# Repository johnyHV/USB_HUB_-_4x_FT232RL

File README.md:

# USB_HUB_-_4x_FT232RL

- USB HUB with FE1.1 chip
- 4x FTDI FT-232RL chip
- 1,8V, 3,3V, 5V logic level

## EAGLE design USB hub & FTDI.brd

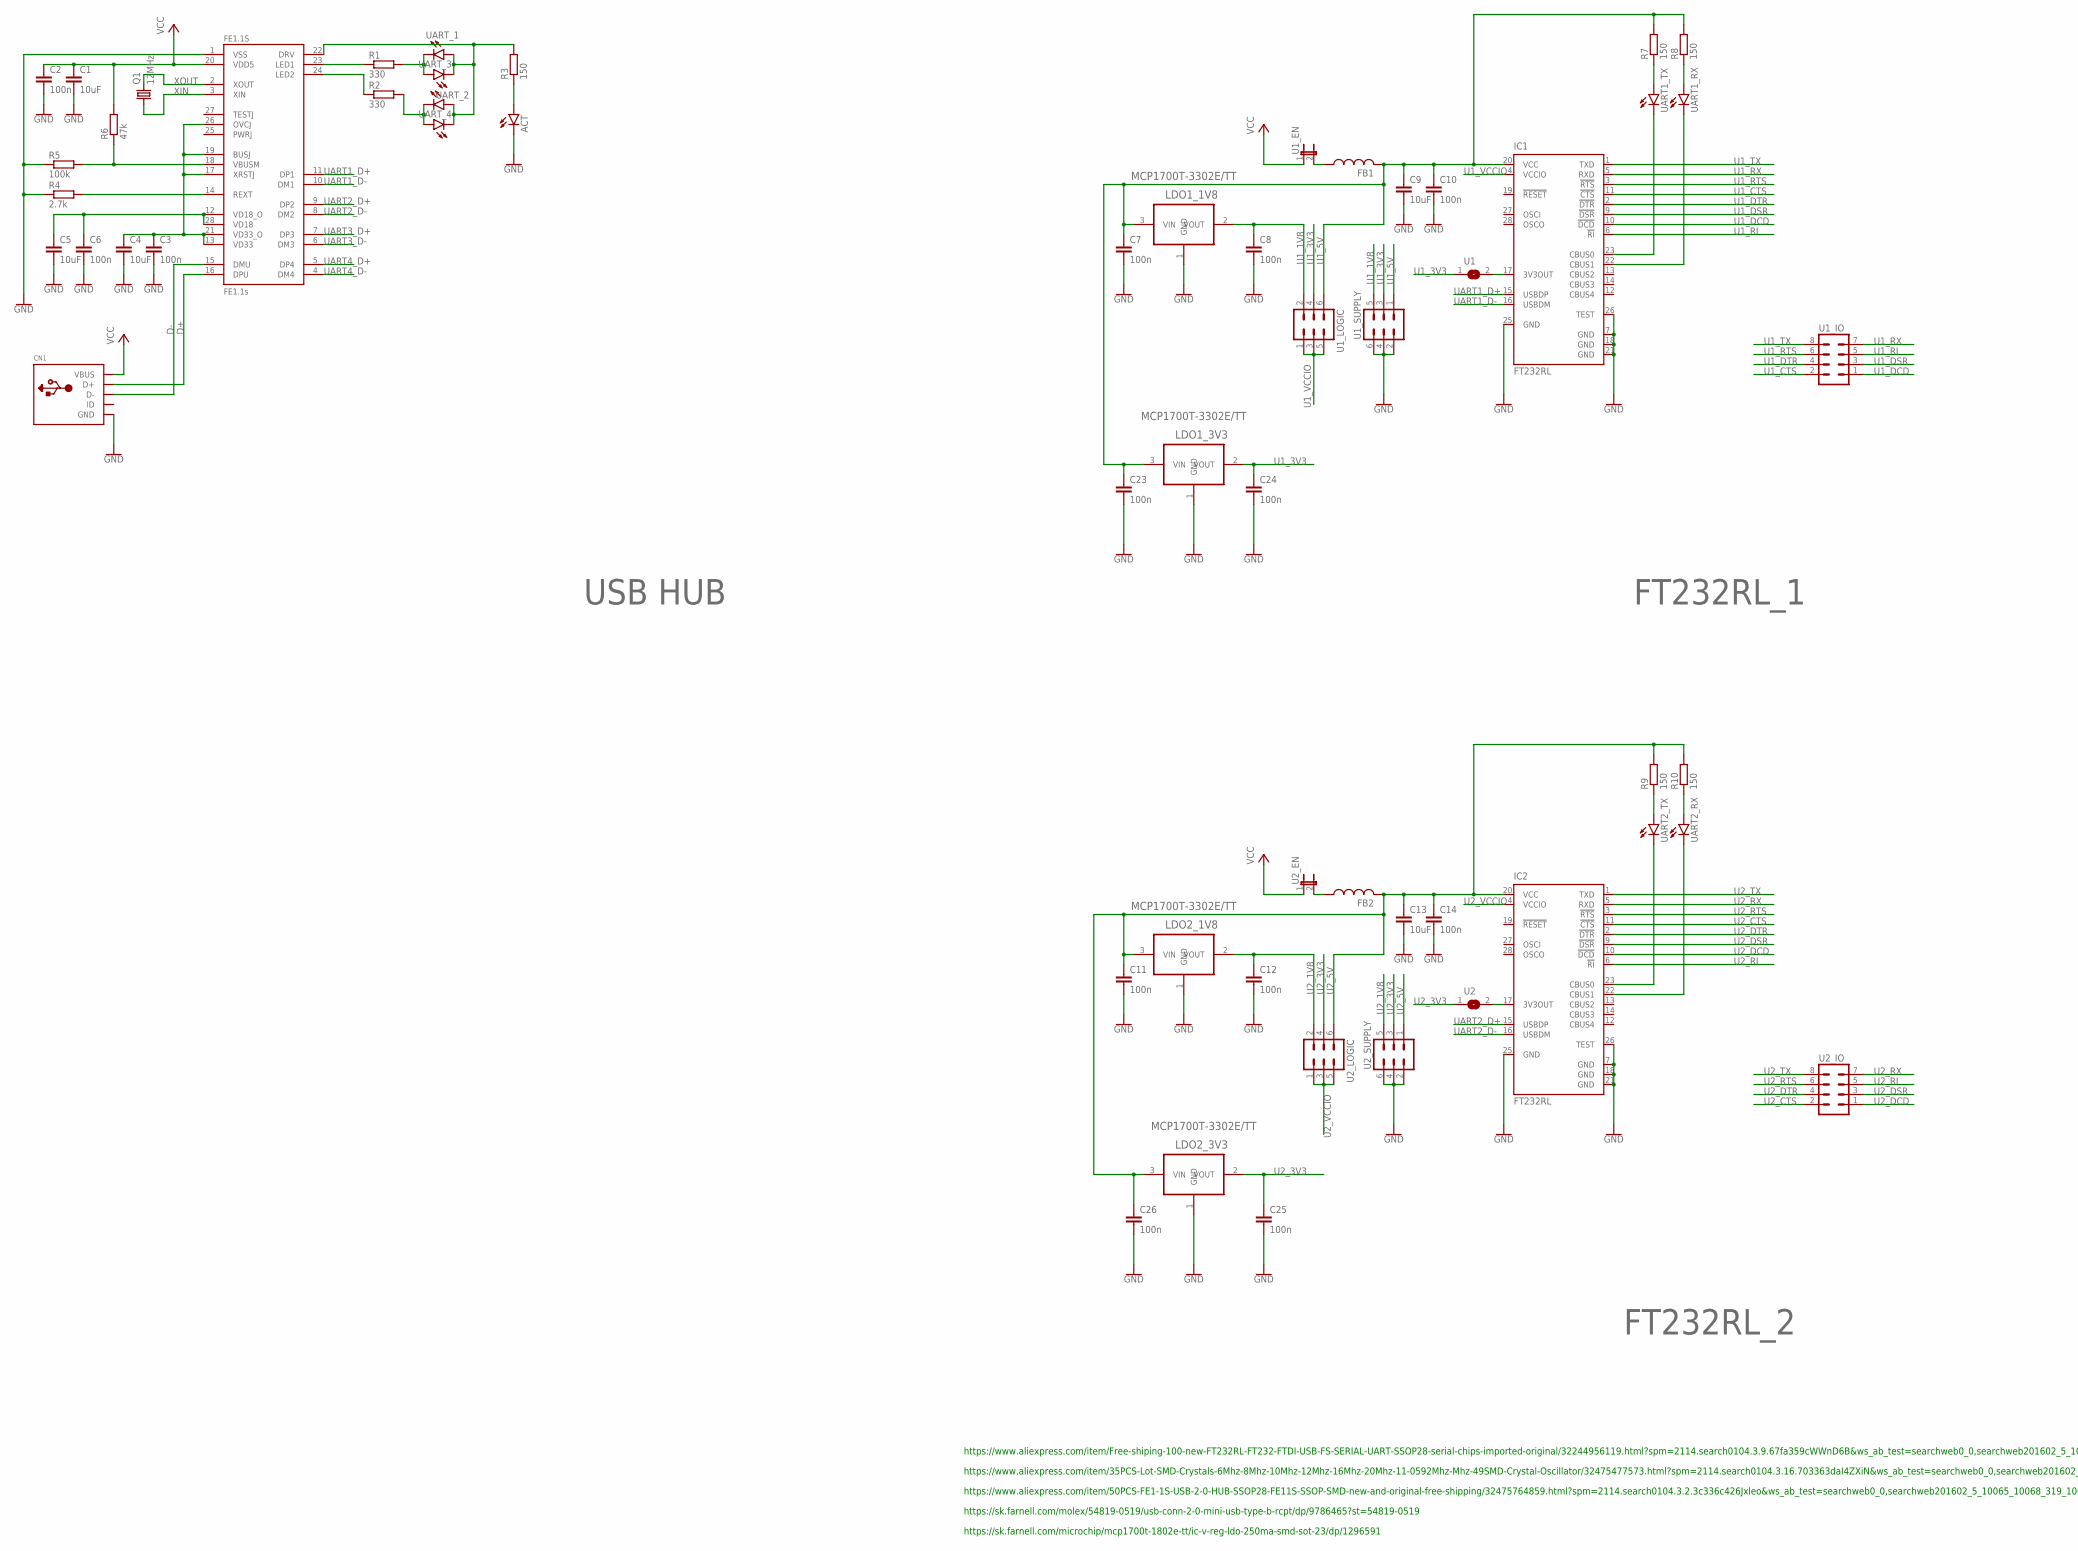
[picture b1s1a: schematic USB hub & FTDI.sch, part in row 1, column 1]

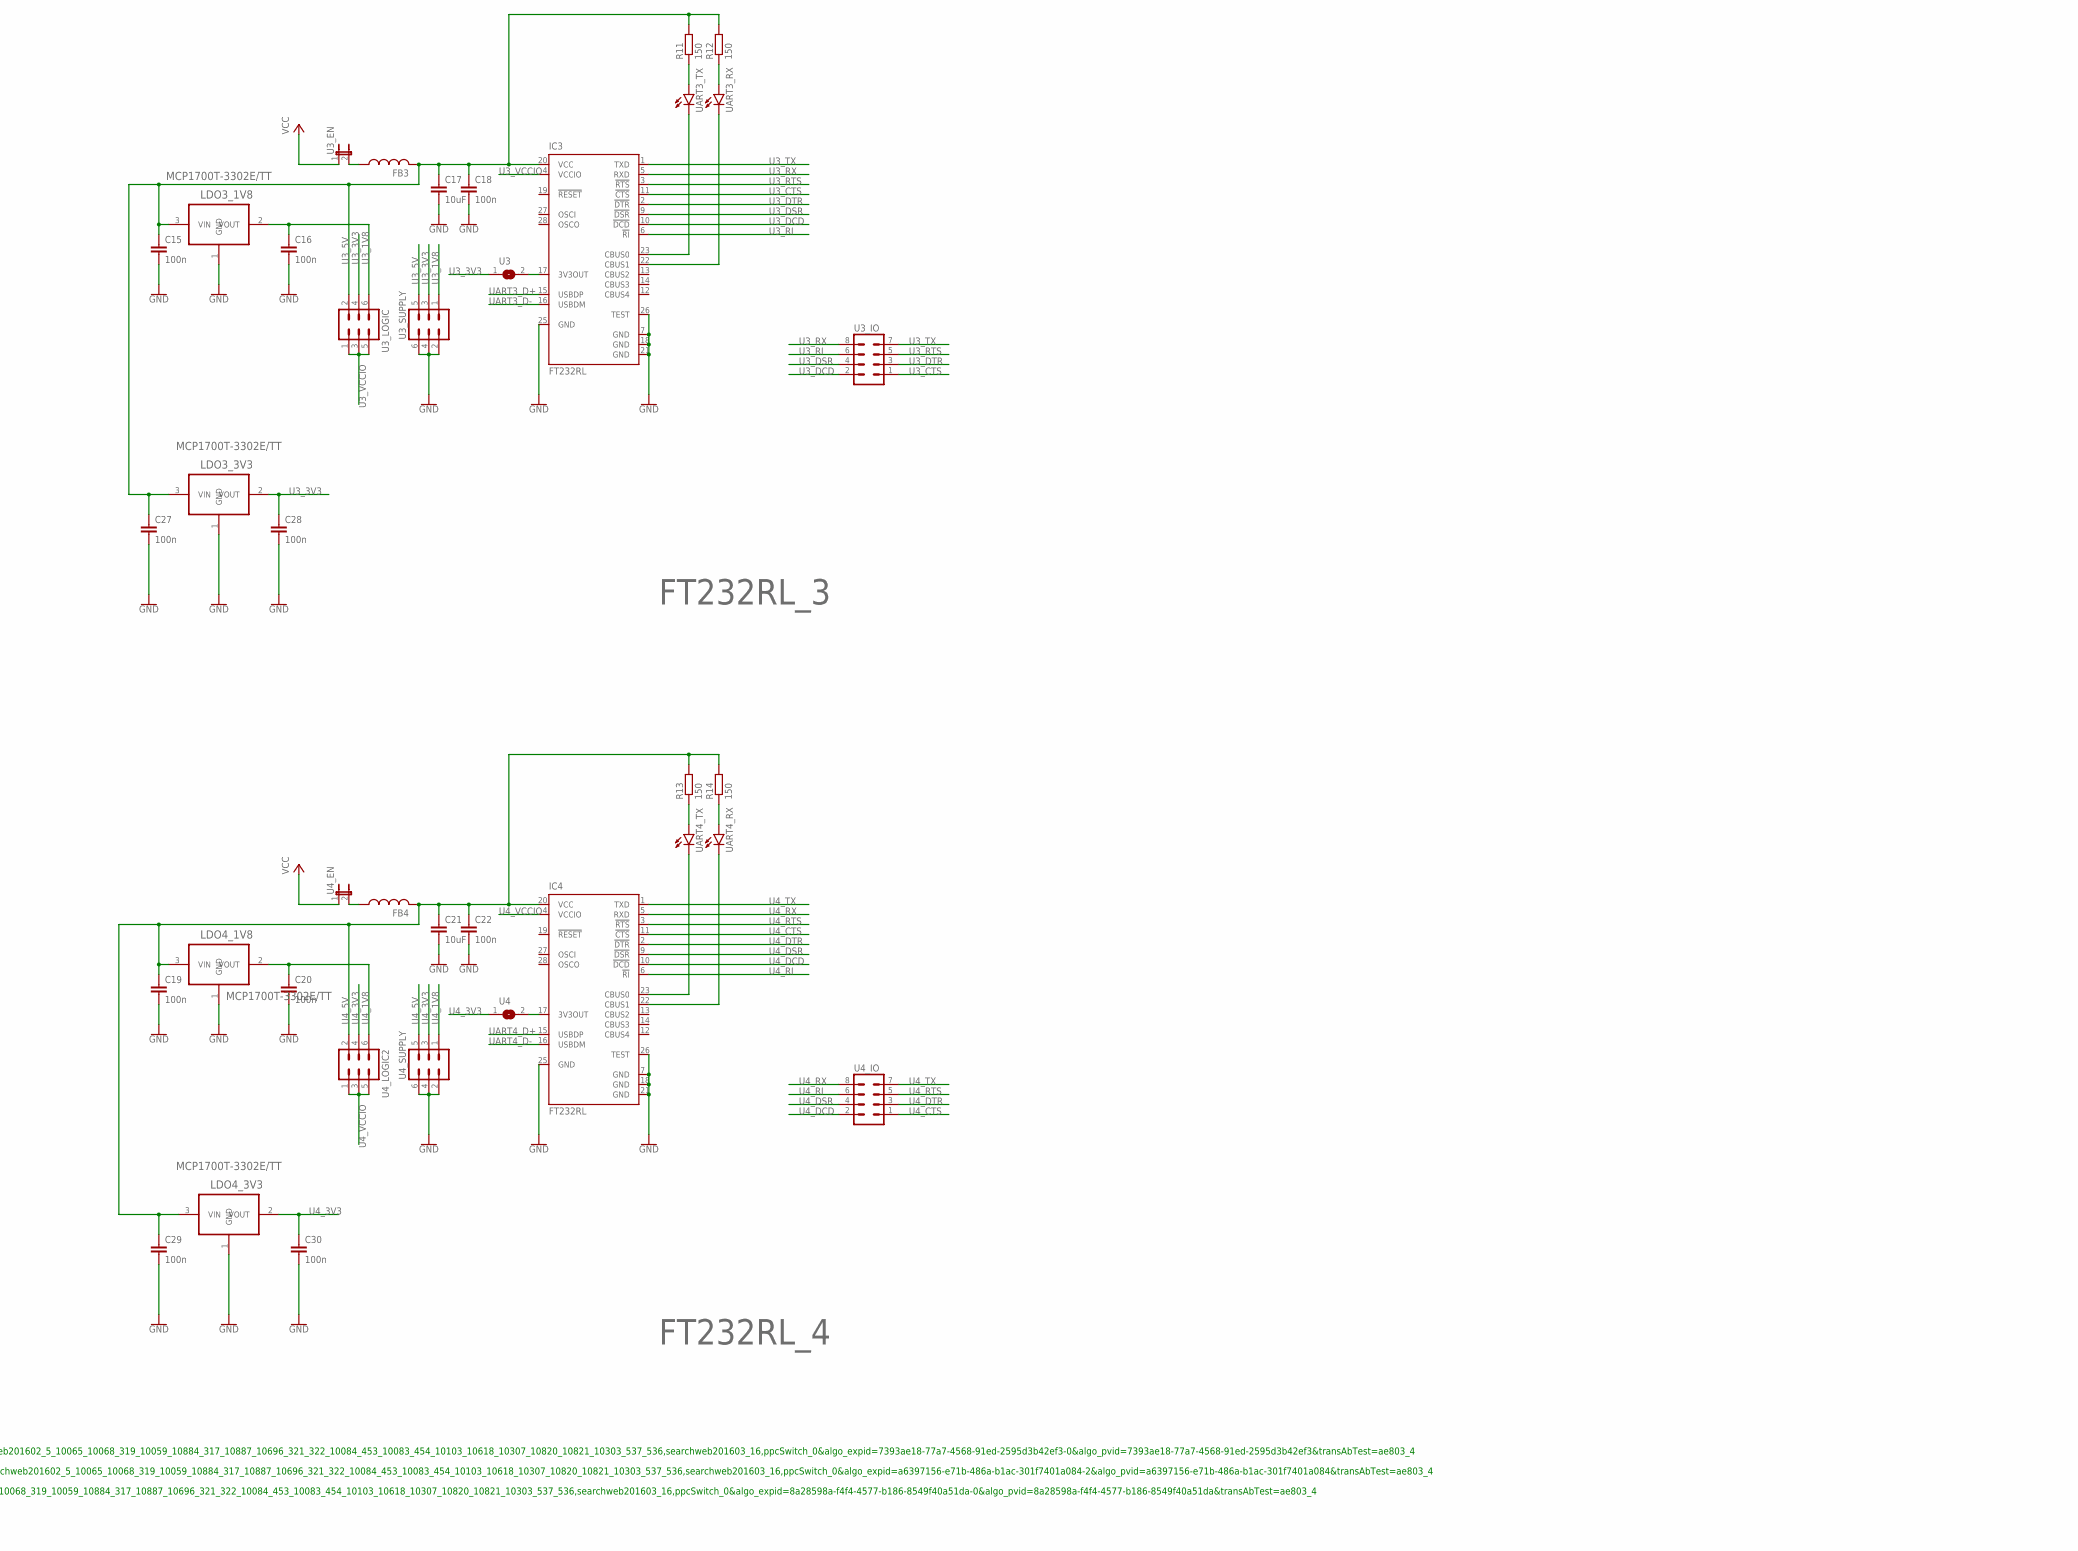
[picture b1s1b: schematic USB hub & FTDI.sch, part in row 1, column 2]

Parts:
ACT: LEDCHIP-LED0805; CHIP-LED0805
C1, C4, C5, C9, C13, C17, C21: 10uF; C0805
C2, C3, C6, C7, C8, C10, C11, C12, C14, C15, C16, C18, C19, C20, C22, C23, C24, C25, C26, C27, C28, C29, C30: 100n; C0805
CN1: USBMOLEX; USB-MINIB-THM-MOLEX
FB1, FB2, FB3, FB4: FERRITE-BEADB; 0805
FE1.1S: FE1.1S; FE1.1S_SSOP-28
IC1, IC2, IC3, IC4: FT232RL; SSOP28
LDO1_1V8, LDO1_3V3, LDO2_1V8, LDO2_3V3, LDO3_1V8, LDO3_3V3, LDO4_1V8, LDO4_3V3: MCP1700T-3302E/TT; SOT95P237X112-3N
Q1: 12MHz; HC49UP
R1, R2: 330; R0805W
R3, R7, R8, R9, R10, R11, R12, R13, R14: 150; R0805W
R4: 2.7k; R0805W
R5: 100k; R0805W
R6: 47k; R0805W
U1, U2, U3, U4: SJ
U1_EN, U2_EN, U3_EN, U4_EN: JP1E; JP1
U1_IO, U2_IO, U3_IO, U4_IO: MA04-2
U1_LOGIC, U1_SUPPLY, U2_LOGIC, U2_SUPPLY, U3_LOGIC, U3_SUPPLY, U4_LOGIC2, U4_SUPPLY: MA03-2
UART1_RX, UART1_TX, UART2_RX, UART2_TX, UART3_RX, UART3_TX, UART4_RX, UART4_TX: LEDCHIP-LED0805; CHIP-LED0805
UART_1, UART_2, UART_3, UART_4: LEDCHIP-LED0805; CHIP-LED0805

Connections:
D+: CN1.D+, FE1.1S.16 (DPU)
D-: CN1.D-, FE1.1S.15 (DMU)
GND: ACT.C, C1.2, C2.2, C3.2, C4.2, C5.2, C6.2, C7.2, C8.2, C9.2, C10.2, C11.2, C12.2, C13.2, C14.2, C15.2, C16.2, C17.2, C18.2, C19.2, C20.2, C21.2, C22.2, C23.2, C24.2, C25.2, C26.2, C27.2, C28.2, C29.2, C30.2, CN1.GND, FE1.1S.1 (VSS), IC1.7 (GND), IC1.18 (GND), IC1.21 (GND), IC1.25 (GND), IC1.26 (TEST), IC2.7 (GND), IC2.18 (GND), IC2.21 (GND), IC2.25 (GND), IC2.26 (TEST), IC3.7 (GND), IC3.18 (GND), IC3.21 (GND), IC3.25 (GND), IC3.26 (TEST), IC4.7 (GND), IC4.18 (GND), IC4.21 (GND), IC4.25 (GND), IC4.26 (TEST), LDO1_1V8.1 (GND), LDO1_3V3.1 (GND), LDO2_1V8.1 (GND), LDO2_3V3.1 (GND), LDO3_1V8.1 (GND), LDO3_3V3.1 (GND), LDO4_1V8.1 (GND), LDO4_3V3.1 (GND), R4.1, R5.1, U1_SUPPLY.2, U1_SUPPLY.4, U1_SUPPLY.6, U2_SUPPLY.2, U2_SUPPLY.4, U2_SUPPLY.6, U3_SUPPLY.2, U3_SUPPLY.4, U3_SUPPLY.6, U4_SUPPLY.2, U4_SUPPLY.4, U4_SUPPLY.6
unnamed: FE1.1S.23 (LED1), R1.1
unnamed: FE1.1S.24 (LED2), R2.1
unnamed: R1.2, UART_1.C, UART_3.A
unnamed: R2.2, UART_2.C, UART_4.A
unnamed: C5.1, C6.1, FE1.1S.12 (VD18_O), FE1.1S.28 (VD18)
unnamed: R9.1, UART2_TX.A
unnamed: FE1.1S.22 (DRV), R3.2, UART_1.A, UART_2.A, UART_3.C, UART_4.C
unnamed: R7.1, UART1_TX.A
unnamed: ACT.A, R3.1
unnamed: FE1.1S.18 (VBUSM), R5.2, R6.1
unnamed: FE1.1S.14 (REXT), R4.2
unnamed: C3.1, C4.1, FE1.1S.13 (VD33), FE1.1S.17 (XRSTJ), FE1.1S.19 (BUSJ), FE1.1S.21 (VD33_O), FE1.1S.26 (OVCJ)
unnamed: R8.1, UART1_RX.A
unnamed: IC1.23 (CBUS0), UART1_TX.C
unnamed: IC1.22 (CBUS1), UART1_RX.C
unnamed: R10.1, UART2_RX.A
unnamed: IC2.23 (CBUS0), UART2_TX.C
unnamed: IC2.22 (CBUS1), UART2_RX.C
unnamed: FB2.1, U2_EN.2
unnamed: R11.1, UART3_TX.A
unnamed: R12.1, UART3_RX.A
unnamed: IC3.23 (CBUS0), UART3_TX.C
unnamed: IC3.22 (CBUS1), UART3_RX.C
unnamed: FB3.1, U3_EN.2
unnamed: FB1.1, U1_EN.2
unnamed: R13.1, UART4_TX.A
unnamed: R14.1, UART4_RX.A
unnamed: IC4.23 (CBUS0), UART4_TX.C
unnamed: IC4.22 (CBUS1), UART4_RX.C
unnamed: FB4.1, U4_EN.2
unnamed: IC1.17 (3V3OUT), U1.2
unnamed: IC2.17 (3V3OUT), U2.2
unnamed: IC3.17 (3V3OUT), U3.2
unnamed: IC4.17 (3V3OUT), U4.2
U1_1V8: C8.1, LDO1_1V8.2 (VOUT), U1_LOGIC.2, U1_SUPPLY.5
U1_3V3: C24.1, LDO1_3V3.2 (VOUT), U1.1, U1_LOGIC.4, U1_SUPPLY.3
U1_5V: C7.1, C9.1, C10.1, C23.1, FB1.2, IC1.20 (VCC), LDO1_1V8.3 (VIN), LDO1_3V3.3 (VIN), R7.2, R8.2, U1_LOGIC.6, U1_SUPPLY.1
U1_CTS: IC1.11 (!CTS), U1_IO.2
U1_DCD: IC1.10 (!DCD), U1_IO.1
U1_DSR: IC1.9 (!DSR), U1_IO.3
U1_DTR: IC1.2 (!DTR), U1_IO.4
U1_RI: IC1.6 (!RI), U1_IO.5
U1_RTS: IC1.3 (!RTS), U1_IO.6
U1_RX: IC1.5 (RXD), U1_IO.7
U1_TX: IC1.1 (TXD), U1_IO.8
U1_VCCIO: IC1.4 (VCCIO), U1_LOGIC.1, U1_LOGIC.3, U1_LOGIC.5
U2_1V8: C12.1, LDO2_1V8.2 (VOUT), U2_LOGIC.2, U2_SUPPLY.5
U2_3V3: C25.1, LDO2_3V3.2 (VOUT), U2.1, U2_LOGIC.4, U2_SUPPLY.3
U2_5V: C11.1, C13.1, C14.1, C26.1, FB2.2, IC2.20 (VCC), LDO2_1V8.3 (VIN), LDO2_3V3.3 (VIN), R9.2, R10.2, U2_LOGIC.6, U2_SUPPLY.1
U2_CTS: IC2.11 (!CTS), U2_IO.2
U2_DCD: IC2.10 (!DCD), U2_IO.1
U2_DSR: IC2.9 (!DSR), U2_IO.3
U2_DTR: IC2.2 (!DTR), U2_IO.4
U2_RI: IC2.6 (!RI), U2_IO.5
U2_RTS: IC2.3 (!RTS), U2_IO.6
U2_RX: IC2.5 (RXD), U2_IO.7
U2_TX: IC2.1 (TXD), U2_IO.8
U2_VCCIO: IC2.4 (VCCIO), U2_LOGIC.1, U2_LOGIC.3, U2_LOGIC.5
U3_1V8: C16.1, LDO3_1V8.2 (VOUT), U3_LOGIC.6, U3_SUPPLY.1
U3_3V3: C28.1, LDO3_3V3.2 (VOUT), U3.1, U3_LOGIC.4, U3_SUPPLY.3
U3_5V: C15.1, C17.1, C18.1, C27.1, FB3.2, IC3.20 (VCC), LDO3_1V8.3 (VIN), LDO3_3V3.3 (VIN), R11.2, R12.2, U3_LOGIC.2, U3_SUPPLY.5
U3_CTS: IC3.11 (!CTS), U3_IO.1
U3_DCD: IC3.10 (!DCD), U3_IO.2
U3_DSR: IC3.9 (!DSR), U3_IO.4
U3_DTR: IC3.2 (!DTR), U3_IO.3
U3_RI: IC3.6 (!RI), U3_IO.6
U3_RTS: IC3.3 (!RTS), U3_IO.5
U3_RX: IC3.5 (RXD), U3_IO.8
U3_TX: IC3.1 (TXD), U3_IO.7
U3_VCCIO: IC3.4 (VCCIO), U3_LOGIC.1, U3_LOGIC.3, U3_LOGIC.5
U4_1V8: C20.1, LDO4_1V8.2 (VOUT), U4_LOGIC2.6, U4_SUPPLY.1
U4_3V3: C30.1, LDO4_3V3.2 (VOUT), U4.1, U4_LOGIC2.4, U4_SUPPLY.3
U4_5V: C19.1, C21.1, C22.1, C29.1, FB4.2, IC4.20 (VCC), LDO4_1V8.3 (VIN), LDO4_3V3.3 (VIN), R13.2, R14.2, U4_LOGIC2.2, U4_SUPPLY.5
U4_CTS: IC4.11 (!CTS), U4_IO.1
U4_DCD: IC4.10 (!DCD), U4_IO.2
U4_DSR: IC4.9 (!DSR), U4_IO.4
U4_DTR: IC4.2 (!DTR), U4_IO.3
U4_RI: IC4.6 (!RI), U4_IO.6
U4_RTS: IC4.3 (!RTS), U4_IO.5
U4_RX: IC4.5 (RXD), U4_IO.8
U4_TX: IC4.1 (TXD), U4_IO.7
U4_VCCIO: IC4.4 (VCCIO), U4_LOGIC2.1, U4_LOGIC2.3, U4_LOGIC2.5
UART1_D+: FE1.1S.11 (DP1), IC1.15 (USBDP)
UART1_D-: FE1.1S.10 (DM1), IC1.16 (USBDM)
UART2_D+: FE1.1S.9 (DP2), IC2.15 (USBDP)
UART2_D-: FE1.1S.8 (DM2), IC2.16 (USBDM)
UART3_D+: FE1.1S.7 (DP3), IC3.15 (USBDP)
UART3_D-: FE1.1S.6 (DM3), IC3.16 (USBDM)
UART4_D+: FE1.1S.5 (DP4), IC4.15 (USBDP)
UART4_D-: FE1.1S.4 (DM4), IC4.16 (USBDM)
VCC: C1.1, C2.1, CN1.VBUS, FE1.1S.20 (VDD5), R6.2, U1_EN.1, U2_EN.1, U3_EN.1, U4_EN.1
XIN: FE1.1S.3 (XIN), Q1.1
XOUT: FE1.1S.2 (XOUT), Q1.2

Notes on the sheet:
https://www.aliexpress.com/item/Free-shiping-100-new-FT232RL-FT232-FTDI-USB-FS-SERIAL-UART-SSOP28-serial-chips-imported-original/32244956119.html?spm=2114.search0104.3.9.67fa359cWWnD6B&ws_ab_test=searchweb0_0,searchweb201602_5_10065_10068_319_10059_10884_317_10887_10696_321_322_10084_453_10083_454_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
https://www.aliexpress.com/item/35PCS-Lot-SMD-Crystals-6Mhz-8Mhz-10Mhz-12Mhz-16Mhz-20Mhz-11-0592Mhz-Mhz-49SMD-Crystal-Oscillator/32475477573.html?spm=2114.search0104.3.16.703363daI4ZXiN&ws_ab_test=searchweb0_0,searchweb201602_5_10065_10068_319_10059_10884_317_10887_10696_321_322_10084_453_10083_454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
https://www.aliexpress.com/item/50PCS-FE1-1S-USB-2-0-HUB-SSOP28-FE11S-SSOP-SMD-new-and-original-free-shipping/32475764859.html?spm=2114.search0104.3.2.3c336c426Jxleo&ws_ab_test=searchweb0_0,searchweb201602_5_10065_10068_319_10059_10884_317_10887_10696_321_322_10084_453_10083_454_10103_10618_10307_1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
https://sk.farnell.com/molex/54819-0519/usb-conn-2-0-mini-usb-type-b-rcpt/dp/9786465?st=54819-0519
https://sk.farnell.com/microchip/mcp1700t-1802e-tt/ic-v-reg-ldo-250ma-smd-sot-23/dp/1296591
USB HUB
FT232RL_1
FT232RL_2
FT232RL_3
FT232RL_4

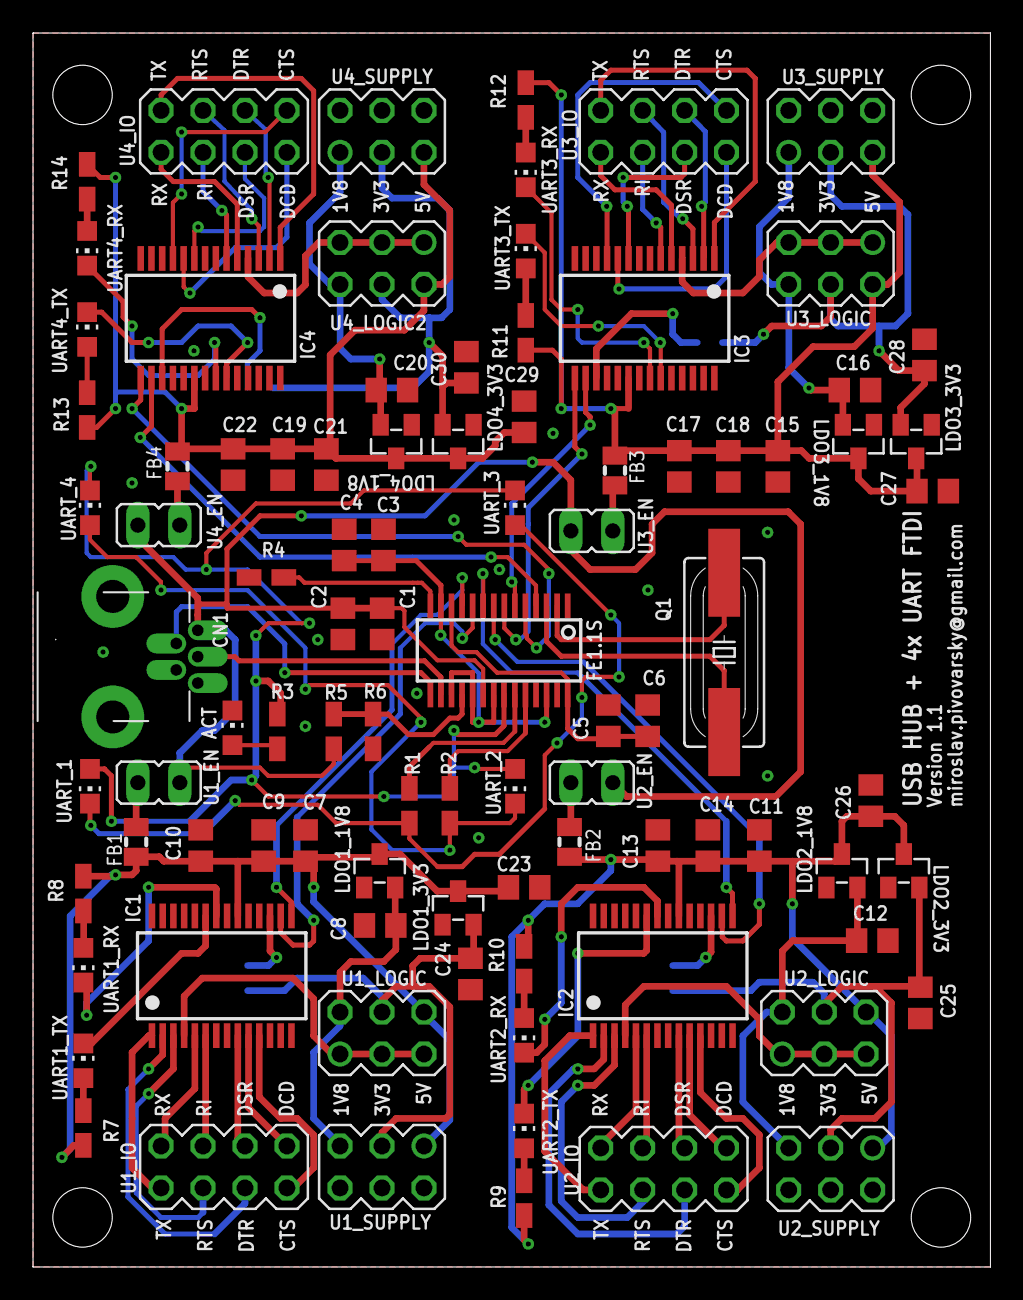
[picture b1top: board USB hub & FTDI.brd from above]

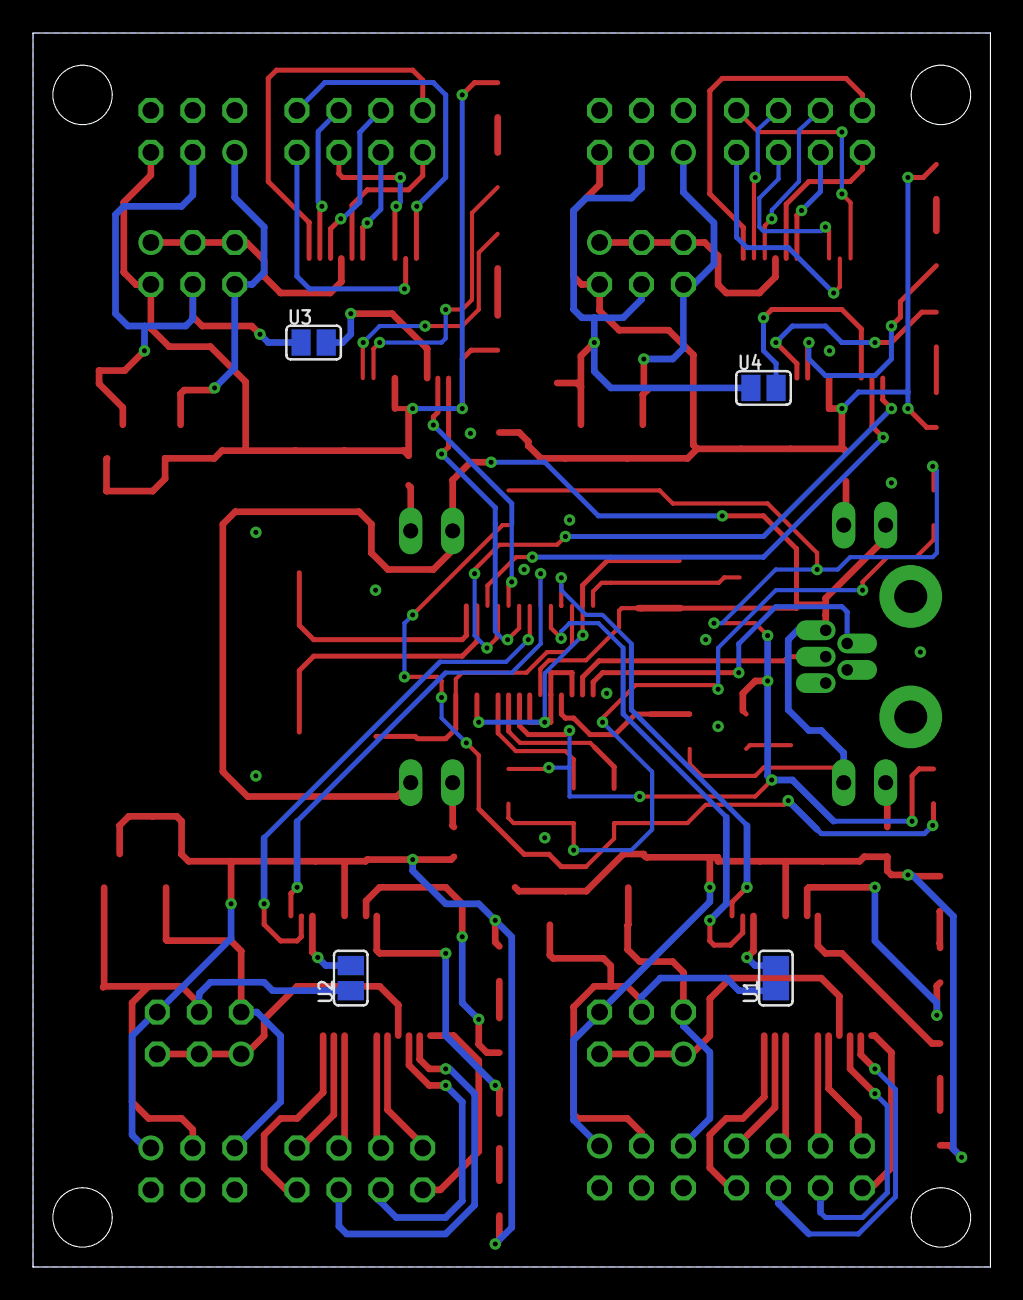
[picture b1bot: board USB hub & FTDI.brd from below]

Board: 2 copper layers, 58.0 x 74.8 mm, 96 parts (4 on the bottom side), 96 nets.

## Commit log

2020-05-18 Init commit
2020-05-26 [Docu]
    - Add author
2020-11-17 [docu]
    - update photos

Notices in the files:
parts and their libraries:
m-pad-2.1: License : GNU General Public License version 2 (see bottom)
SparkFun-PowerSymbols: Licensing: Creative Commons ShareAlike 4.0 International - https://creativecommons.org/licenses/by-sa/4.0
